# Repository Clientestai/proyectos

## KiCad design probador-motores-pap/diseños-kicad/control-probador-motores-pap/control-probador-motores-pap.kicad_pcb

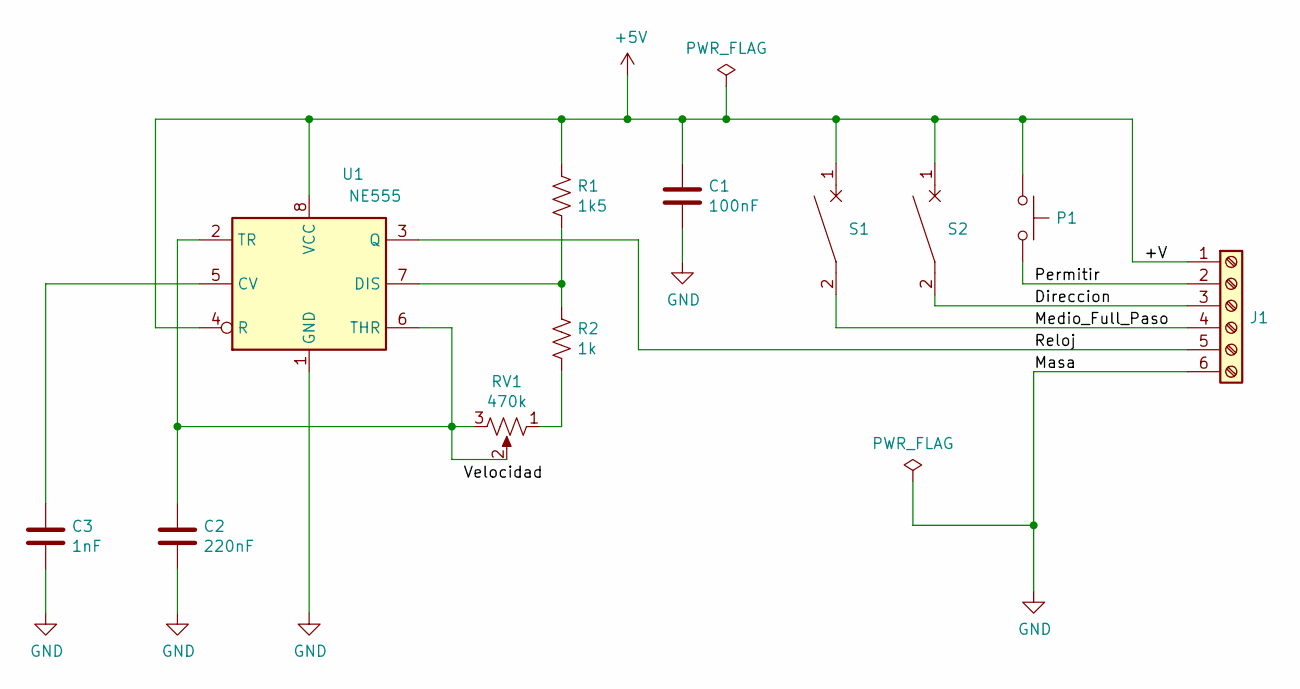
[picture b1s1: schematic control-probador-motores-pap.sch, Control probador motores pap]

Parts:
C1: 100nF; C_Rect_L10.0mm_W4.0mm_P7.50mm_MKS4
C2: 220nF; C_Rect_L10.0mm_W4.0mm_P7.50mm_MKS4
C3: 1nF; C_Rect_L10.0mm_W4.0mm_P7.50mm_MKS4
J1: Screw_Terminal_01x06; TerminalBlock_Phoenix_MKDS-1,5-6-5.08_1x06_P5.08mm_Horizont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
P1: SW_Push; PhoenixContact_MKDS_1,5_2-1727010-1x02_P3.50mm
R1: 1k5; R_Axial_DIN0309_L9.0mm_D3.2mm_P12.70mm_Horizontal
R2: 1k; R_Axial_DIN0309_L9.0mm_D3.2mm_P12.70mm_Horizontal
RV1: 470k; PhoenixContact_MKDS_1,5_3-19325191-1x03_P3.50mm
S1, S2: CircuitBreaker_1P; PhoenixContact_MKDS_1,5_2-1727010-1x02_P3.50mm
U1: NE555; DIP-8_W7.62mm

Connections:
+5V: C1.1, J1.1, P1.1, R1.1, S1.1, S2.1, U1.4 (R), U1.8 (VCC)
/Direccion: J1.3, S2.2
/Medio_Full_Paso: J1.4, S1.2
/Permitir: J1.2, P1.2
/Reloj: J1.5, U1.3 (Q)
GND: C1.2, C2.2, C3.2, J1.6, U1.1 (GND)
unnamed: C2.1, RV1.2, RV1.3, U1.2 (TR), U1.6 (THR)
unnamed: C3.1, U1.5 (CV)
unnamed: R1.2, R2.1, U1.7 (DIS)
unnamed: R2.2, RV1.1

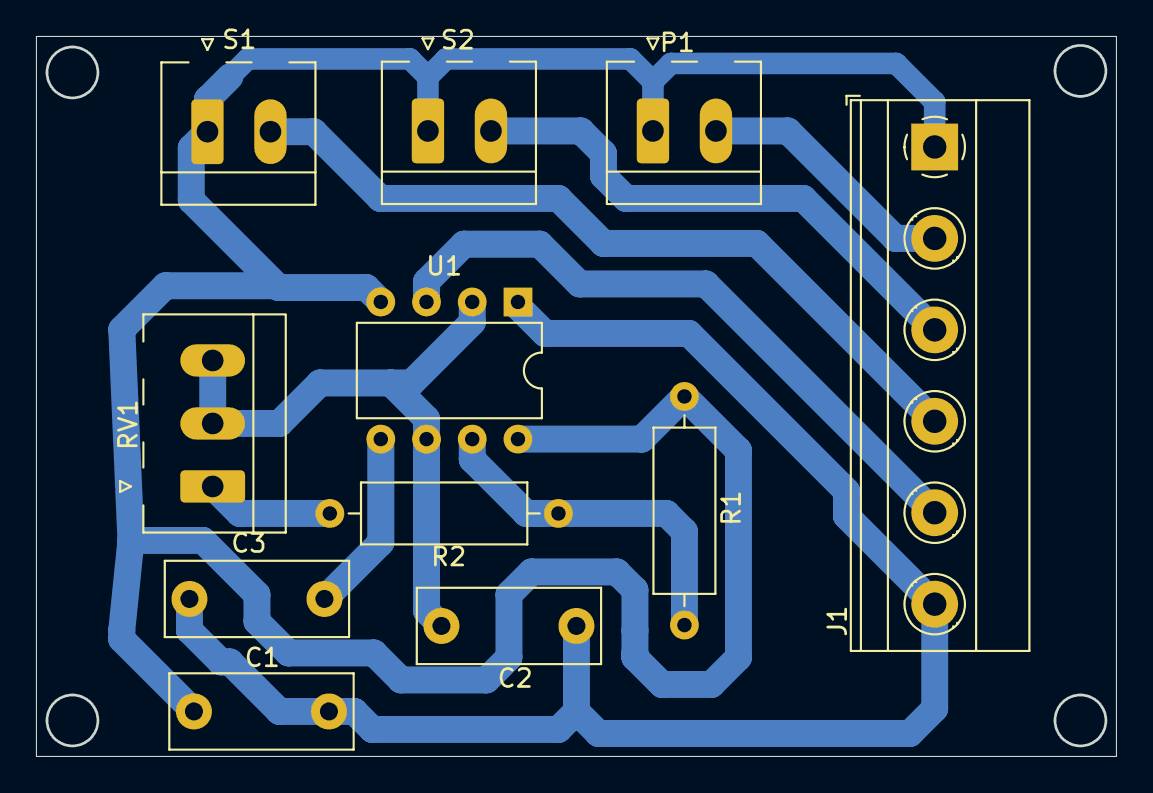
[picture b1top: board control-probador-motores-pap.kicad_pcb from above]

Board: 2 copper layers, 59.9 x 39.9 mm, 11 parts (0 on the bottom side), 10 nets.

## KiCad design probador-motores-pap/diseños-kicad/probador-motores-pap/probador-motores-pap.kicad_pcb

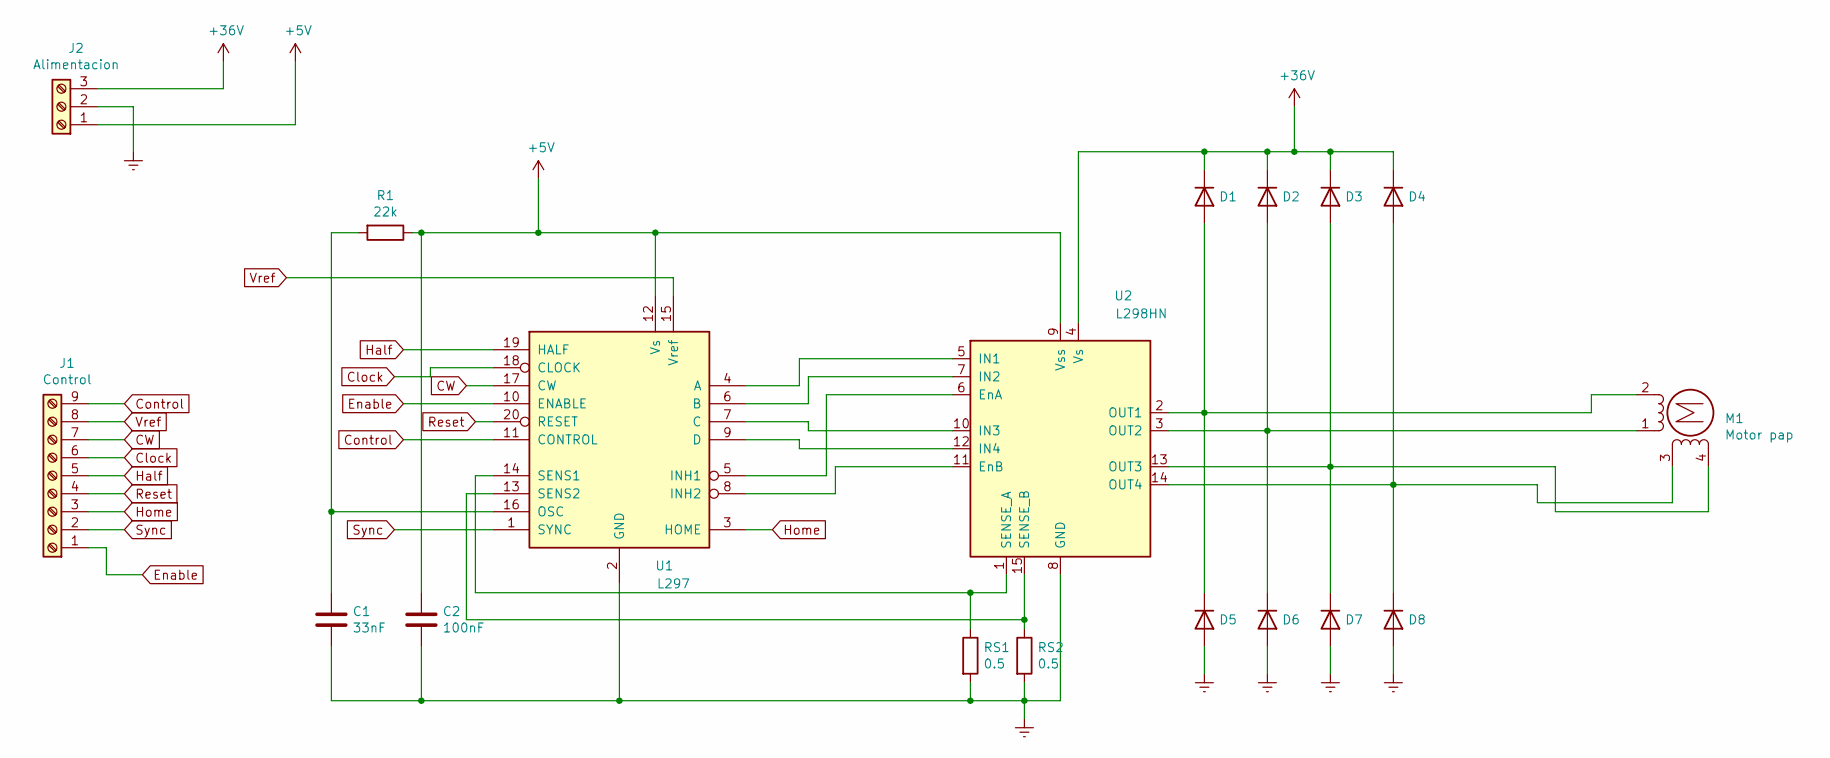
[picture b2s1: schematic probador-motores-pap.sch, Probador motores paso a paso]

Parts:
C1: 33nF; C_Axial_L5.1mm_D3.1mm_P15.00mm_Horizontal
C2: 100nF; C_Axial_L5.1mm_D3.1mm_P7.50mm_Horizontal
D1, D2, D3, D4, D5, D6, D7, D8: 1N4007; D_DO-41_SOD81_P10.16mm_Horizontal
J1: Control; PhoenixContact_MKDS_1,5_9-1715781-1x09_P3.50mm_Horizontal
J2: Alimentacion; PhoenixContact_MKDS_1,5_3-19325191-1x03_P3.50mm
M1: Motor pap; PhoenixContact_MKDS_1,5_4-1715048-1x04_P3.50mm_Horizontal
R1: 22k; R_Axial_DIN0309_L9.0mm_D3.2mm_P12.70mm_Horizontal
RS1, RS2: 0.5; R_Axial_DIN0411_L9.9mm_D3.6mm_P12.70mm_Horizontal
U1: L297; DIP-20_W7.62mm
U2: L298HN; L298-Multiwatt15-V

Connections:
+5V: C2.1, J2.1, R1.1, U1.12 (Vs), U2.9 (Vss)
+36V: D1.1 (K), D2.1 (K), D3.1 (K), D4.1 (K), J2.3, U2.4 (Vs)
CW: J1.7, U1.17 (CW)
Clock: J1.6, U1.18 (CLOCK)
Control: J1.9, U1.11 (CONTROL)
Enable: J1.1, U1.10 (ENABLE)
GNDREF: C1.2, C2.2, D5.2 (A), D6.2 (A), D7.2 (A), D8.2 (A), J2.2, RS1.2, RS2.2, U1.2 (GND), U2.8 (GND)
Half: J1.5, U1.19 (HALF)
Home: J1.3, U1.3 (HOME)
unnamed: C1.1, R1.2, U1.16 (OSC)
unnamed: D1.2 (A), D5.1 (K), M1.2 (-), U2.2 (OUT1)
unnamed: D2.2 (A), D6.1 (K), M1.1, U2.3 (OUT2)
unnamed: D3.2 (A), D7.1 (K), M1.4, U2.13 (OUT3)
unnamed: D4.2 (A), D8.1 (K), M1.3, U2.14 (OUT4)
unnamed: RS1.1, U1.14 (SENS1), U2.1 (SENSE_A)
unnamed: RS2.1, U1.13 (SENS2), U2.15 (SENSE_B)
unnamed: U1.4 (A), U2.5 (IN1)
unnamed: U1.5 (INH1), U2.6 (EnA)
unnamed: U1.6 (B), U2.7 (IN2)
unnamed: U1.7 (C), U2.10 (IN3)
unnamed: U1.8 (INH2), U2.11 (EnB)
unnamed: U1.9 (D), U2.12 (IN4)
Reset: J1.4, U1.20 (RESET)
Sync: J1.2, U1.1 (SYNC)
Vref: J1.8, U1.15 (Vref)

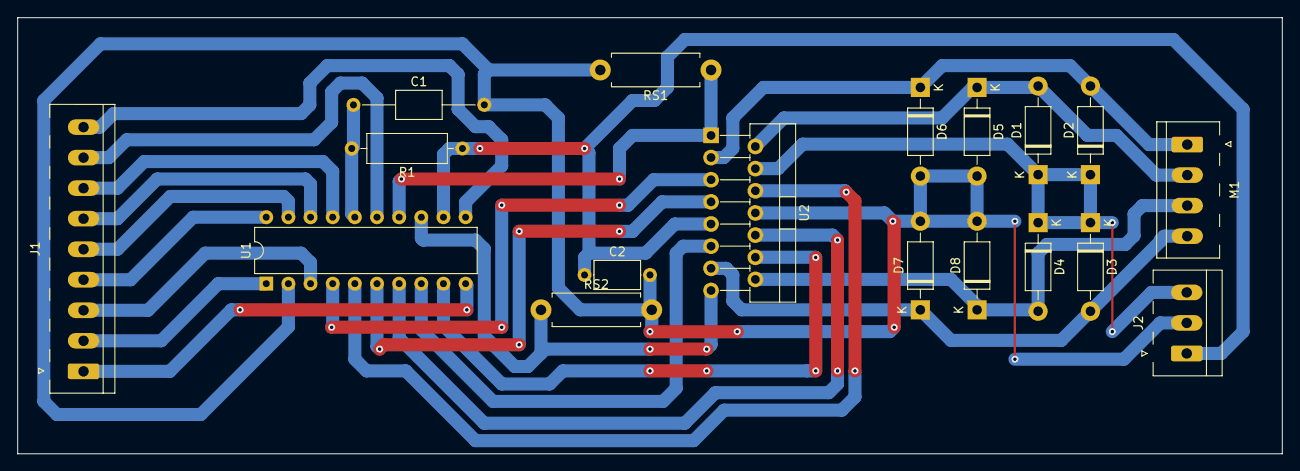
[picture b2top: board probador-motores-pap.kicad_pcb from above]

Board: 2 copper layers, 145.0 x 50.0 mm, 18 parts (0 on the bottom side), 25 nets.

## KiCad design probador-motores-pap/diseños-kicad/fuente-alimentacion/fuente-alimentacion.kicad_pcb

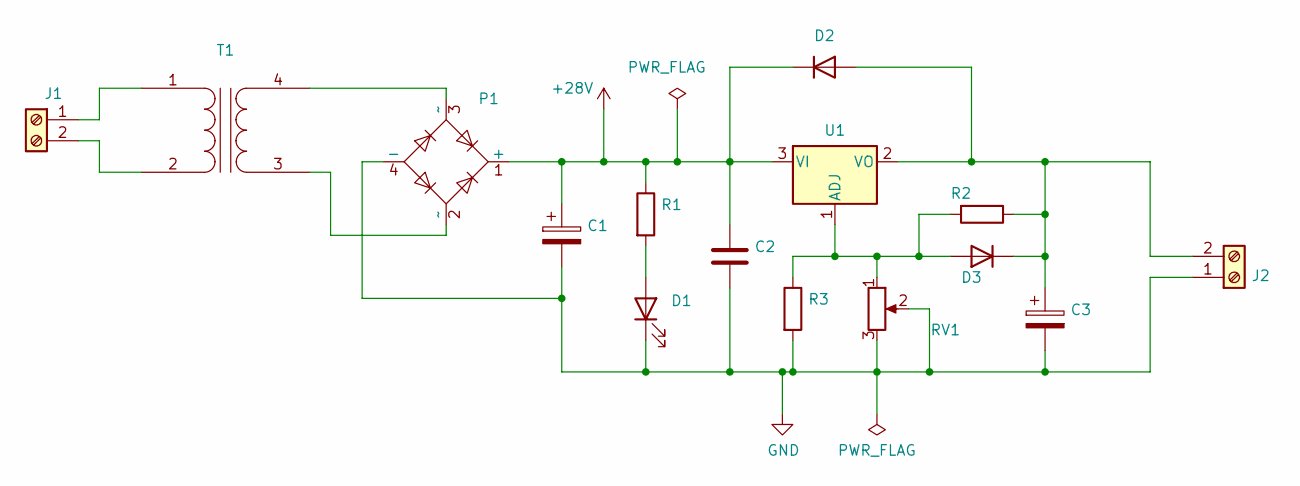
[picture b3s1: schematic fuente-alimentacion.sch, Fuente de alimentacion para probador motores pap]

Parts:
C1: 10000uF_63V; CP_Radial_D8.0mm_P2.50mm
C2: 0.1uF; C_Axial_L5.1mm_D3.1mm_P7.50mm_Horizontal
C3: 2200uF_63V; CP_Radial_D8.0mm_P2.50mm
D1: LED; LED_D8.0mm
D2, D3: 1N4007; D_5W_P5.08mm_Vertical_AnodeUp
J1, J2: Screw_Terminal_01x02; PhoenixContact_MKDS_1,5_2-1727010-1x02_P3.50mm
P1: KBU8J; Diode_Bridge_Vishay_KBU
R1: 2k7_1/4W; R_Axial_DIN0309_L9.0mm_D3.2mm_P15.24mm_Horizontal
R2: 12k_1/4W; R_Axial_DIN0309_L9.0mm_D3.2mm_P12.70mm_Horizontal
R3: 220_1/4W; R_Axial_DIN0309_L9.0mm_D3.2mm_P12.70mm_Horizontal
RV1: 10k; Potentiometer_Bourns_3266Z_Horizontal
T1: VCM 25/1/24; Transformador-VCM_25_1_24
U1: LM338_TO220; TO-220-3_Vertical

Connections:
+28V: C1.1, C2.1, D2.1 (K), P1.1 (+), R1.1, U1.3 (VI)
GND: C1.2, C2.2, C3.2, D1.1 (K), J2.1, P1.4 (-), R3.2, RV1.2, RV1.3
unnamed: C3.1, D2.2 (A), D3.1 (K), J2.2, R2.1, U1.2 (VO)
unnamed: D1.2 (A), R1.2
unnamed: D3.2 (A), R2.2, R3.1, RV1.1, U1.1 (ADJ)
unnamed: J1.1, T1.1 (AA)
unnamed: J1.2, T1.2 (AB)
unnamed: P1.2 (~~), T1.3 (SA)
unnamed: P1.3 (~~), T1.4 (SB)

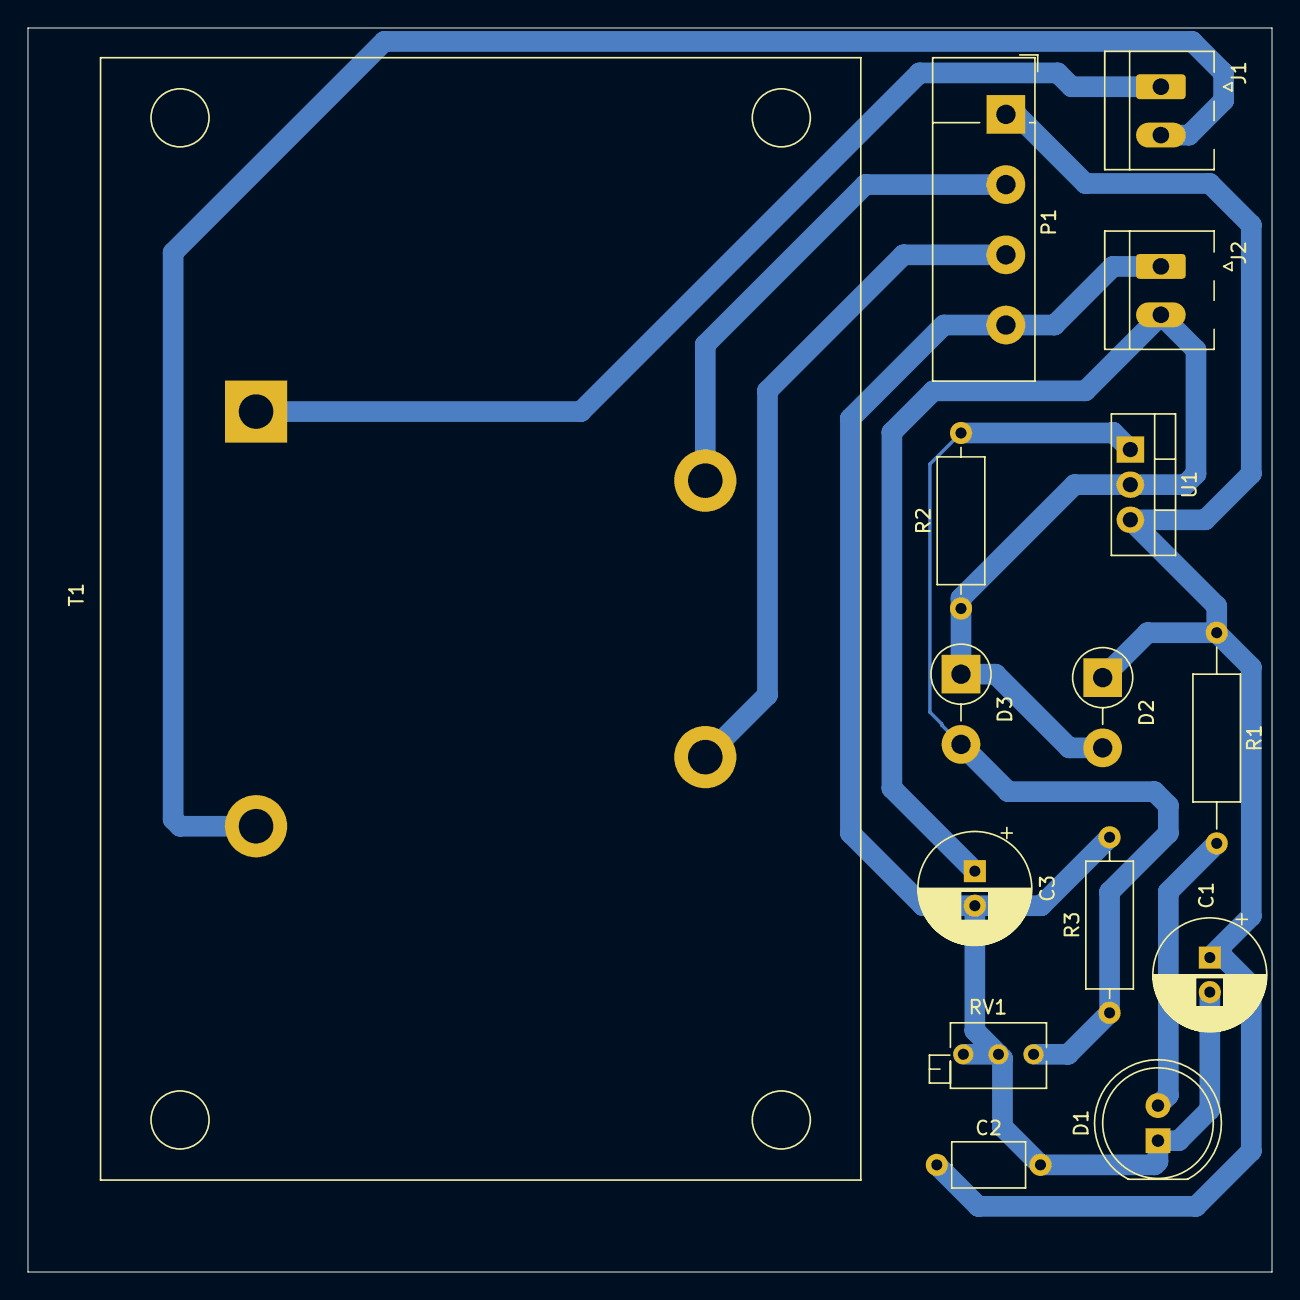
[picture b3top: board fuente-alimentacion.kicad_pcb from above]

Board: 2 copper layers, 90.0 x 90.0 mm, 15 parts (0 on the bottom side), 9 nets.

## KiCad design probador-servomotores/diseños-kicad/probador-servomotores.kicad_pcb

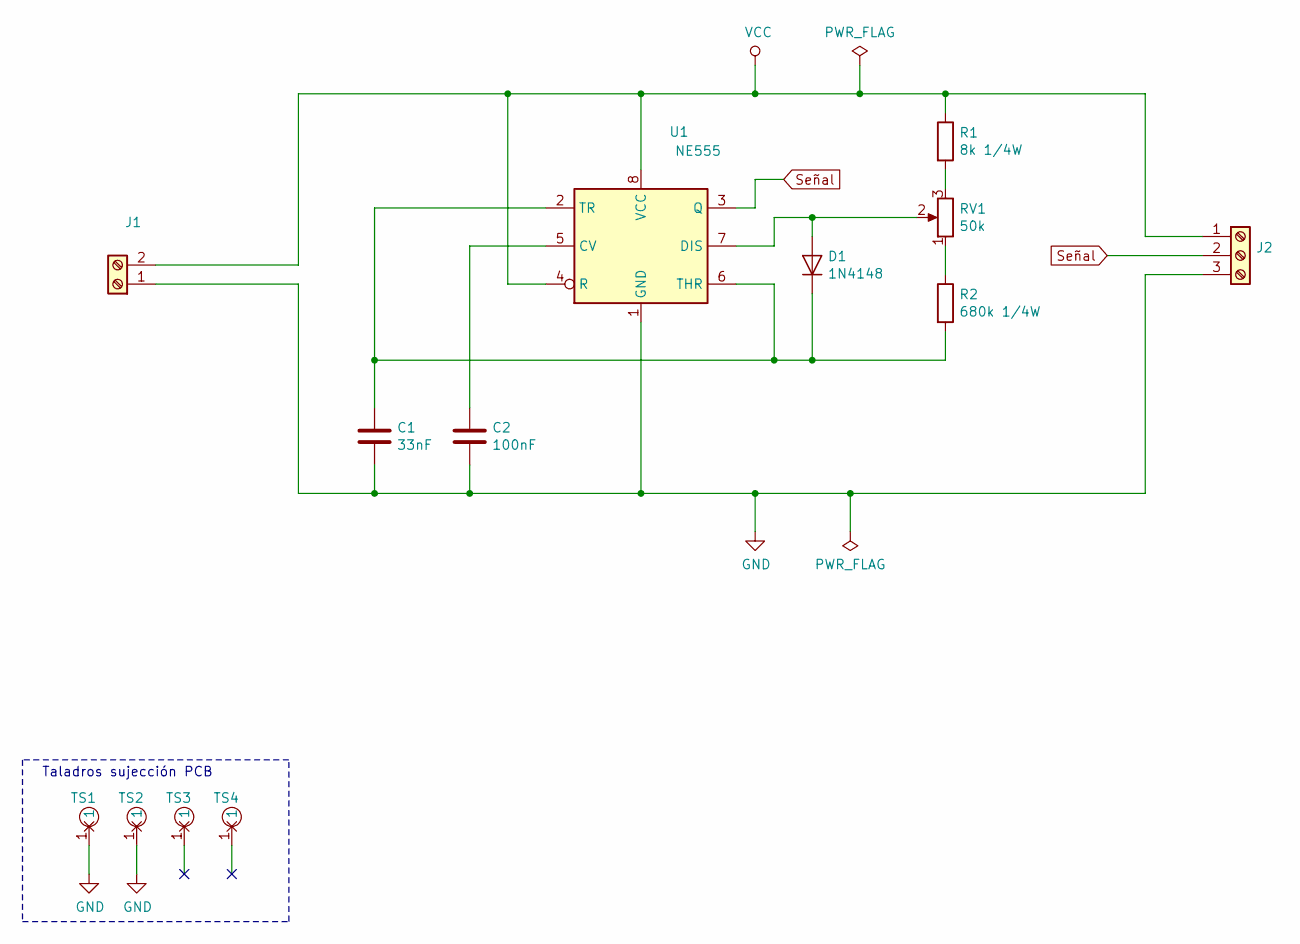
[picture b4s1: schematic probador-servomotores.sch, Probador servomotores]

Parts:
C1: 33nF; C_Disc_D8.0mm_W2.5mm_P5.00mm
C2: 100nF; C_Disc_D8.0mm_W2.5mm_P5.00mm
D1: 1N4148; D_DO-35_SOD27_P7.62mm_Horizontal
J1: Vin de 4.5V a 6V; PhoenixContact_MKDS_1,5_2-1727010-1x02_P3.50mm
J2: Screw_Terminal_01x03; PhoenixContact_MKDS_1,5_3-19325191-1x03_P3.50mm
R1: 8k 1/4W; R_Axial_DIN0309_L9.0mm_D3.2mm_P12.70mm_Horizontal
R2: 680k 1/4W; R_Axial_DIN0309_L9.0mm_D3.2mm_P12.70mm_Horizontal
RV1: 50k; Potentiometer_ACP_CA9-V10_Vertical_Hole
TS1, TS2, TS3, TS4: Taladro_Sujeccion; Taladro_Sujecion_3mm
U1: NE555; DIP-8_W7.62mm

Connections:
GND: C1.2, C2.2, J1.1, J2.3, TS1.1, TS2.1, U1.1 (GND)
unnamed: C1.1, D1.1 (K), R2.2, U1.2 (TR), U1.6 (THR)
unnamed: C2.1, U1.5 (CV)
unnamed: D1.2 (A), RV1.2, U1.7 (DIS)
unnamed: R1.2, RV1.3
unnamed: R2.1, RV1.1
Señal: J2.2, U1.3 (Q)
VCC: J1.2, J2.1, R1.1, U1.4 (R), U1.8 (VCC)

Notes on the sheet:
Taladros sujección PCB

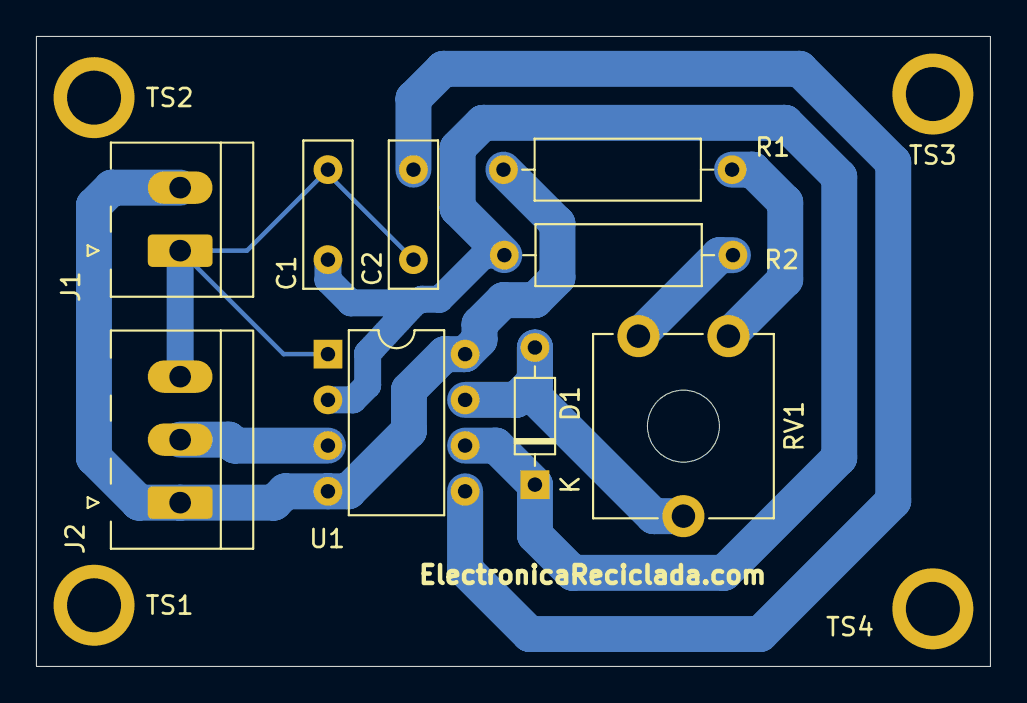
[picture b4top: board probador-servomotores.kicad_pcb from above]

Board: 2 copper layers, 53.0 x 35.0 mm, 13 parts (0 on the bottom side), 8 nets.
